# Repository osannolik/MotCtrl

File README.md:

MotCtrl
=========================== 

A small inverter for brushless motors. 

## Hardware

* Microcontroller STM32F446, ARM Cortex-M4, 180 MHz, FPU
* Power MOSFETs 60 V, 300 A, 1.1 mOhm FDBL0110N60
* High- and low-side gate drivers LM5101A
* Inline phase current sensing using INA240 amplifiers
* Hall-sensor inputs
* Standard servo (PPM/PWM) input
* Motor and board temp sensor (NTC)
* Expansion header for UART/ADC/DAC/SPI/I2C/CAN
* PCB size 45x77 mm

# License
GNU GPLv3 (both hardware and experimental software)

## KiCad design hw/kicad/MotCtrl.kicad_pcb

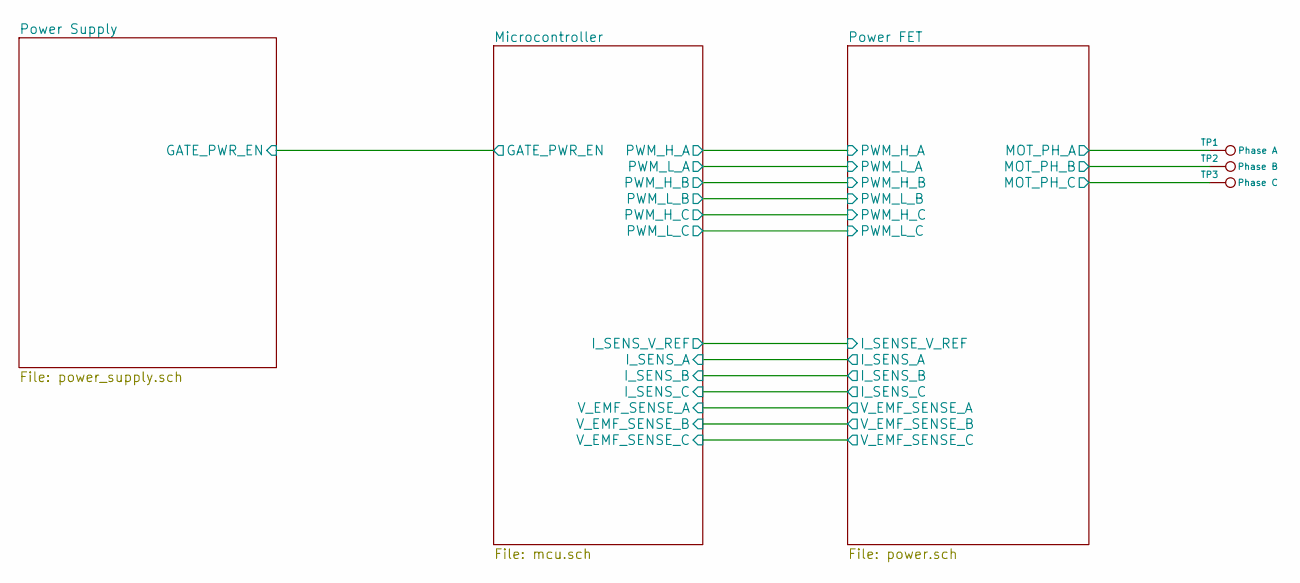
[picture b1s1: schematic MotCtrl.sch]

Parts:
TP1: Phase A; SolderWirePad_single_SMD_5x10mm
TP2: Phase B; SolderWirePad_single_SMD_5x10mm
TP3: Phase C; SolderWirePad_single_SMD_5x10mm

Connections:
/Power FET/MOT_PH_A: TP1.1; also elsewhere on the board
/Power FET/MOT_PH_B: TP2.1; also elsewhere on the board
/Power FET/MOT_PH_C: TP3.1; also elsewhere on the board

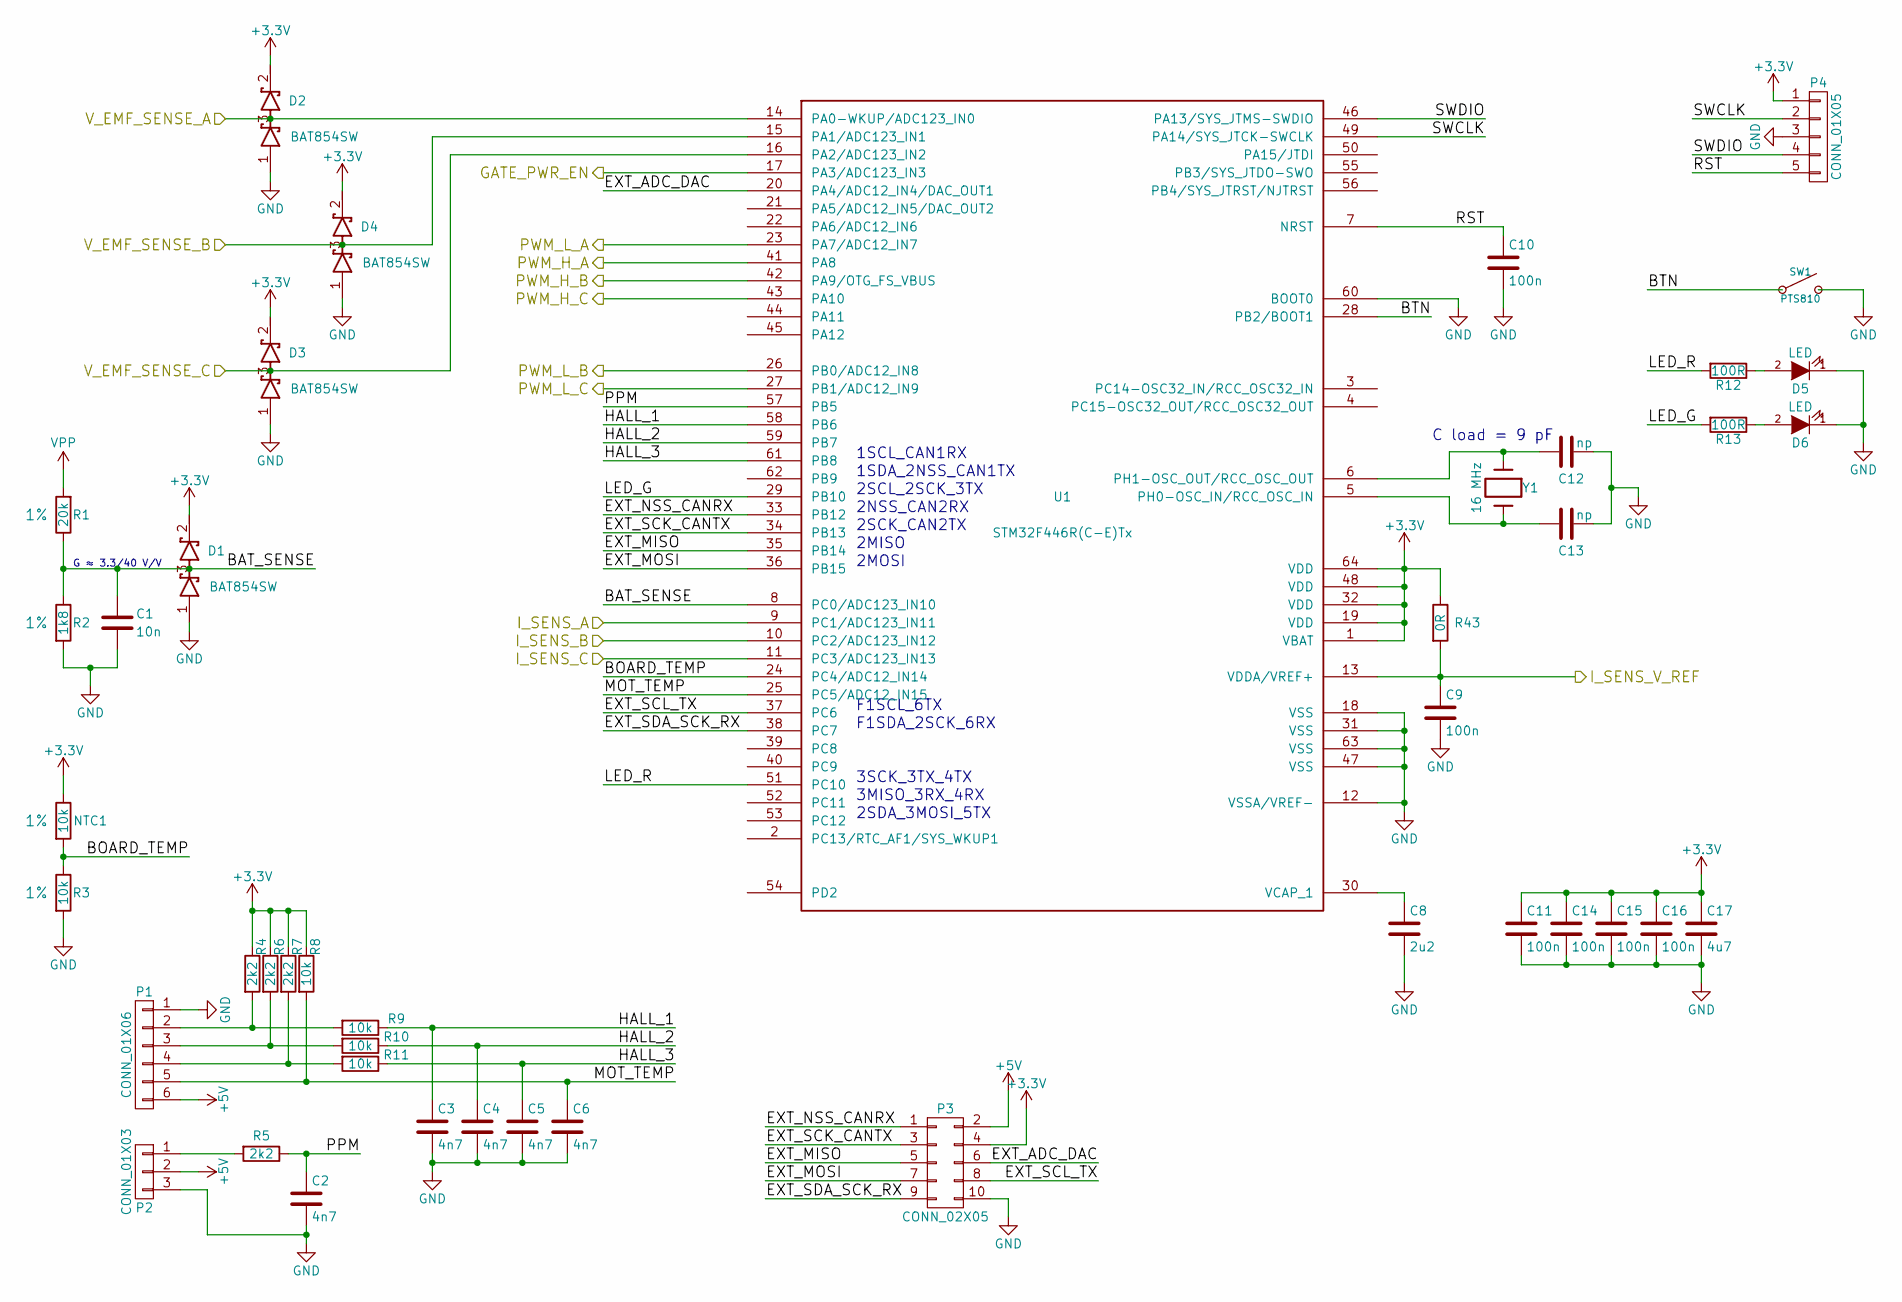
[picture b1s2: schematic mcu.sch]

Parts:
C1: 10n; C_0402
C2, C3, C4, C5, C6: 4n7; C_0402
C8: 2u2; C_0402
C9, C10, C11, C14, C15, C16: 100n; C_0402
C12, C13: np; C_0402
C17: 4u7; C_0603
D1, D2, D3, D4: BAT854SW; SOT-323
D5, D6: LED; LED_0603
NTC1: 10k; R_0603; Tolerance 1%
P1: CONN_01X06; JST_ZH_B6B-ZR
P2: CONN_01X03; Pin_Header_Straight_1x03
P3: CONN_02X05; Pin_Header_Straight_2x05
P4: CONN_01X05; Pin_Header_Straight_1x05
R1: 20k; R_0402; Tolerance 1%
R2: 1k8; R_0402; Tolerance 1%
R3: 10k; R_0402; Tolerance 1%
R4, R5, R6, R7: 2k2; R_0402
R8, R9, R10, R11: 10k; R_0402
R12, R13: 100R; R_0402
R43: 0R; R_0402
SW1: PTS810
U1: STM32F446R(C-E)Tx; LQFP-64_10x10mm_Pitch0.5mm
Y1: 16 MHz; crystal_FA238-TSX3225

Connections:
+3V3: C11.1, C14.1, C15.1, C16.1, C17.1, D1.2 (K), D2.2 (K), D3.2 (K), D4.2 (K), NTC1.1, P3.4, P4.1, R4.1, R6.1, R7.1, R8.1, R43.1, U1.1 (VBAT), U1.19 (VDD), U1.32 (VDD), U1.48 (VDD), U1.64 (VDD); also elsewhere on the board
+5V: P1.6, P2.2, P3.2; also elsewhere on the board
/Microcontroller/BAT_SENSE: C1.1, D1.3 (common), R1.1, R2.1, U1.8 (PC0/ADC123_IN10); also elsewhere on the board
/Microcontroller/BOARD_TEMP: NTC1.2, R3.1, U1.24 (PC4/ADC12_IN14)
/Microcontroller/BTN: SW1.1, SW1.2, U1.28 (PB2/BOOT1)
/Microcontroller/EXT_ADC_DAC: P3.6, U1.20 (PA4/ADC12_IN4/DAC_OUT1)
/Microcontroller/EXT_MISO: P3.5, U1.35 (PB14)
/Microcontroller/EXT_MOSI: P3.7, U1.36 (PB15)
/Microcontroller/EXT_NSS_CANRX: P3.1, U1.33 (PB12)
/Microcontroller/EXT_SCK_CANTX: P3.3, U1.34 (PB13)
/Microcontroller/EXT_SCL_TX: P3.8, U1.37 (PC6)
/Microcontroller/EXT_SDA_SCK_RX: P3.9, U1.38 (PC7)
/Microcontroller/GATE_PWR_EN: U1.17 (PA3/ADC123_IN3); also elsewhere on the board
/Microcontroller/HALL_1: C3.1, R9.1, U1.58 (PB6)
/Microcontroller/HALL_2: C4.1, R10.1, U1.59 (PB7)
/Microcontroller/HALL_3: C5.1, R11.1, U1.61 (PB8)
/Microcontroller/I_SENS_A: U1.9 (PC1/ADC123_IN11); also elsewhere on the board
/Microcontroller/I_SENS_B: U1.10 (PC2/ADC123_IN12); also elsewhere on the board
/Microcontroller/I_SENS_C: U1.11 (PC3/ADC123_IN13); also elsewhere on the board
/Microcontroller/LED_G: R13.2, U1.29 (PB10)
/Microcontroller/LED_R: R12.2, U1.51 (PC10)
/Microcontroller/MOT_TEMP: C6.1, P1.5, R8.2, U1.25 (PC5/ADC12_IN15)
/Microcontroller/PPM: C2.1, R5.1, U1.57 (PB5)
/Microcontroller/PWM_H_A: U1.41 (PA8); also elsewhere on the board
/Microcontroller/PWM_H_B: U1.42 (PA9/OTG_FS_VBUS); also elsewhere on the board
/Microcontroller/PWM_H_C: U1.43 (PA10); also elsewhere on the board
/Microcontroller/PWM_L_A: U1.23 (PA7/ADC12_IN7); also elsewhere on the board
/Microcontroller/PWM_L_B: U1.26 (PB0/ADC12_IN8); also elsewhere on the board
/Microcontroller/PWM_L_C: U1.27 (PB1/ADC12_IN9); also elsewhere on the board
/Microcontroller/RST: C10.1, P4.5, U1.7 (NRST)
/Microcontroller/SWCLK: P4.2, U1.49 (PA14/SYS_JTCK-SWCLK)
/Microcontroller/SWDIO: P4.4, U1.46 (PA13/SYS_JTMS-SWDIO)
/Microcontroller/V_EMF_SENSE_A: D2.3 (common), U1.14 (PA0-WKUP/ADC123_IN0); also elsewhere on the board
/Microcontroller/V_EMF_SENSE_B: D4.3 (common), U1.15 (PA1/ADC123_IN1); also elsewhere on the board
/Microcontroller/V_EMF_SENSE_C: D3.3 (common), U1.16 (PA2/ADC123_IN2); also elsewhere on the board
/Power FET/I_SENSE_V_REF: C9.1, R43.2, U1.13 (VDDA/VREF+); also elsewhere on the board
GND: C1.2, C2.2, C3.2, C4.2, C5.2, C6.2, C8.2, C9.2, C10.2, C11.2, C12.1, C13.1, C14.2, C15.2, C16.2, C17.2, D1.1 (A), D2.1 (A), D3.1 (A), D4.1 (A), D5.1 (K), D6.1 (K), P1.1, P2.3, P3.10, P4.3, R2.2, R3.2, SW1.3, SW1.4, U1.12 (VSSA/VREF-), U1.18 (VSS), U1.31 (VSS), U1.47 (VSS), U1.60 (BOOT0), U1.63 (VSS); also elsewhere on the board
unnamed: C8.1, U1.30 (VCAP_1)
unnamed: C12.2, U1.6 (PH1-OSC_OUT/RCC_OSC_OUT), Y1.1
unnamed: C13.2, U1.5 (PH0-OSC_IN/RCC_OSC_IN), Y1.2
unnamed: D5.2 (A), R12.1
unnamed: D6.2 (A), R13.1
unnamed: P1.2, R4.2, R9.2
unnamed: P1.3, R6.2, R10.2
unnamed: P1.4, R7.2, R11.2
unnamed: P2.1, R5.2
VPP: R1.2; also elsewhere on the board

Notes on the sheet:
C load = 9 pF
G ≈ 3.3/40 V/V
1SCL_CAN1RX
1SDA_2NSS_CAN1TX
2SCL_2SCK_3TX
2NSS_CAN2RX
2SCK_CAN2TX
2MISO
2MOSI
F1SCL_6TX
F1SDA_2SCK_6RX
3SCK_3TX_4TX
3MISO_3RX_4RX
2SDA_3MOSI_5TX

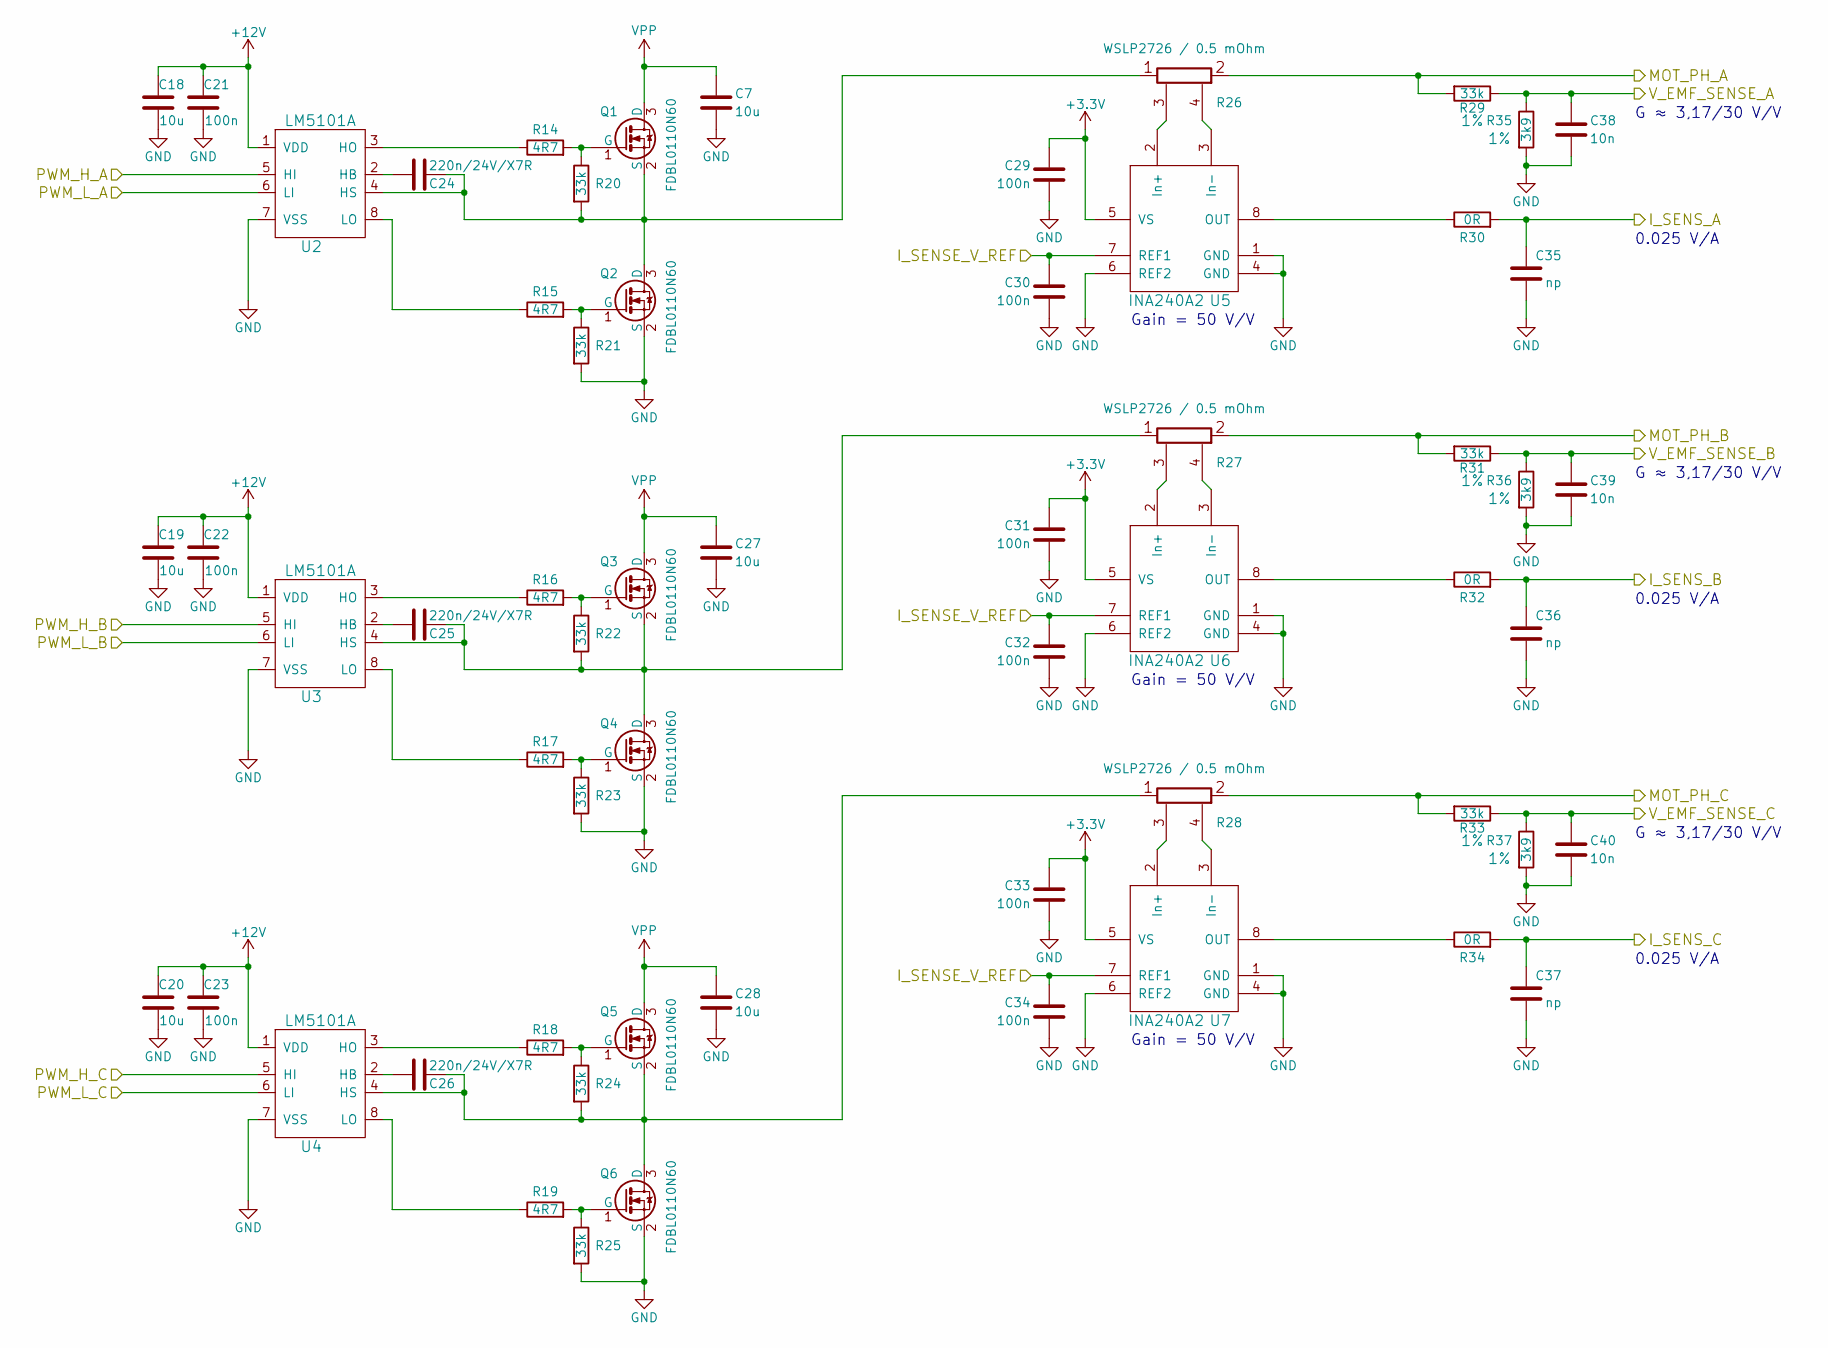
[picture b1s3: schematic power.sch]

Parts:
C7, C27, C28: 10u; C_1210
C18, C19, C20: 10u; C_0805
C21, C22, C23, C29, C30, C31, C32, C33, C34: 100n; C_0402
C24, C25, C26: 220n/24V/X7R; C_0603
C35, C36, C37: np; C_0402
C38, C39, C40: 10n; C_0402
Q1, Q2, Q3, Q4, Q5, Q6: FDBL0110N60; MO-299A
R14, R15, R16, R17, R18, R19: 4R7; R_0402
R20, R21, R22, R23, R24, R25: 33k; R_0402
R26, R27, R28: WSLP2726 / 0.5 mOhm; WSLP2726
R29, R31, R33: 33k; R_0402; Tolerance 1%
R30, R32, R34: 0R; R_0402
R35, R36, R37: 3k9; R_0402; Tolerance 1%
U2, U3, U4: LM5101A; WSON-8
U5, U6, U7: INA240A2; TSSOP-8_4.4x3mm_Pitch0.65mm

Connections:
+3V3: C29.2, C31.2, C33.2, U5.5 (VS), U6.5 (VS), U7.5 (VS); also elsewhere on the board
+12V: C18.2, C19.2, C20.2, C21.2, C22.2, C23.2, U2.1 (VDD), U3.1 (VDD), U4.1 (VDD); also elsewhere on the board
/Microcontroller/I_SENS_A: C35.2, R30.2; also elsewhere on the board
/Microcontroller/I_SENS_B: C36.2, R32.2; also elsewhere on the board
/Microcontroller/I_SENS_C: C37.2, R34.2; also elsewhere on the board
/Microcontroller/PWM_H_A: U2.5 (HI); also elsewhere on the board
/Microcontroller/PWM_H_B: U3.5 (HI); also elsewhere on the board
/Microcontroller/PWM_H_C: U4.5 (HI); also elsewhere on the board
/Microcontroller/PWM_L_A: U2.6 (LI); also elsewhere on the board
/Microcontroller/PWM_L_B: U3.6 (LI); also elsewhere on the board
/Microcontroller/PWM_L_C: U4.6 (LI); also elsewhere on the board
/Microcontroller/V_EMF_SENSE_A: C38.1, R29.1, R35.1; also elsewhere on the board
/Microcontroller/V_EMF_SENSE_B: C39.1, R31.1, R36.1; also elsewhere on the board
/Microcontroller/V_EMF_SENSE_C: C40.1, R33.1, R37.1; also elsewhere on the board
/Power FET/I_SENSE_V_REF: C30.2, C32.2, C34.2, U5.7 (REF1), U6.7 (REF1), U7.7 (REF1); also elsewhere on the board
/Power FET/MOT_PH_A: R26.2, R29.2; also elsewhere on the board
/Power FET/MOT_PH_B: R27.2, R31.2; also elsewhere on the board
/Power FET/MOT_PH_C: R28.2, R33.2; also elsewhere on the board
/Power FET/PH_A: C24.1, Q1.2 (S), Q2.3 (D), R20.2, R26.1, U2.4 (HS)
/Power FET/PH_B: C25.1, Q3.2 (S), Q4.3 (D), R22.2, R27.1, U3.4 (HS)
/Power FET/PH_C: C26.1, Q5.2 (S), Q6.3 (D), R24.2, R28.1, U4.4 (HS)
GND: C7.2, C18.1, C19.1, C20.1, C21.1, C22.1, C23.1, C27.2, C28.2, C29.1, C30.1, C31.1, C32.1, C33.1, C34.1, C35.1, C36.1, C37.1, C38.2, C39.2, C40.2, Q2.2 (S), Q4.2 (S), Q6.2 (S), R21.2, R23.2, R25.2, R35.2, R36.2, R37.2, U2.7 (VSS), U3.7 (VSS), U4.7 (VSS), U5.1 (GND), U5.4 (GND), U5.6 (REF2), U6.1 (GND), U6.4 (GND), U6.6 (REF2), U7.1 (GND), U7.4 (GND), U7.6 (REF2); also elsewhere on the board
unnamed: C24.2, U2.2 (HB)
unnamed: C25.2, U3.2 (HB)
unnamed: C26.2, U4.2 (HB)
unnamed: Q1.1 (G), R14.2, R20.1
unnamed: Q2.1 (G), R15.2, R21.1
unnamed: Q3.1 (G), R16.2, R22.1
unnamed: Q4.1 (G), R17.2, R23.1
unnamed: Q5.1 (G), R18.2, R24.1
unnamed: Q6.1 (G), R19.2, R25.1
unnamed: R14.1, U2.3 (HO)
unnamed: R15.1, U2.8 (LO)
unnamed: R16.1, U3.3 (HO)
unnamed: R17.1, U3.8 (LO)
unnamed: R18.1, U4.3 (HO)
unnamed: R19.1, U4.8 (LO)
unnamed: R26.3, U5.2 (In+)
unnamed: R26.4, U5.3 (In-)
unnamed: R27.3, U6.2 (In+)
unnamed: R27.4, U6.3 (In-)
unnamed: R28.3, U7.2 (In+)
unnamed: R28.4, U7.3 (In-)
unnamed: R30.1, U5.8 (OUT)
unnamed: R32.1, U6.8 (OUT)
unnamed: R34.1, U7.8 (OUT)
VPP: C7.1, C27.1, C28.1, Q1.3 (D), Q3.3 (D), Q5.3 (D); also elsewhere on the board

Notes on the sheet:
Gain = 50 V/V
0.025 V/A
G ≈ 3,17/30 V/V

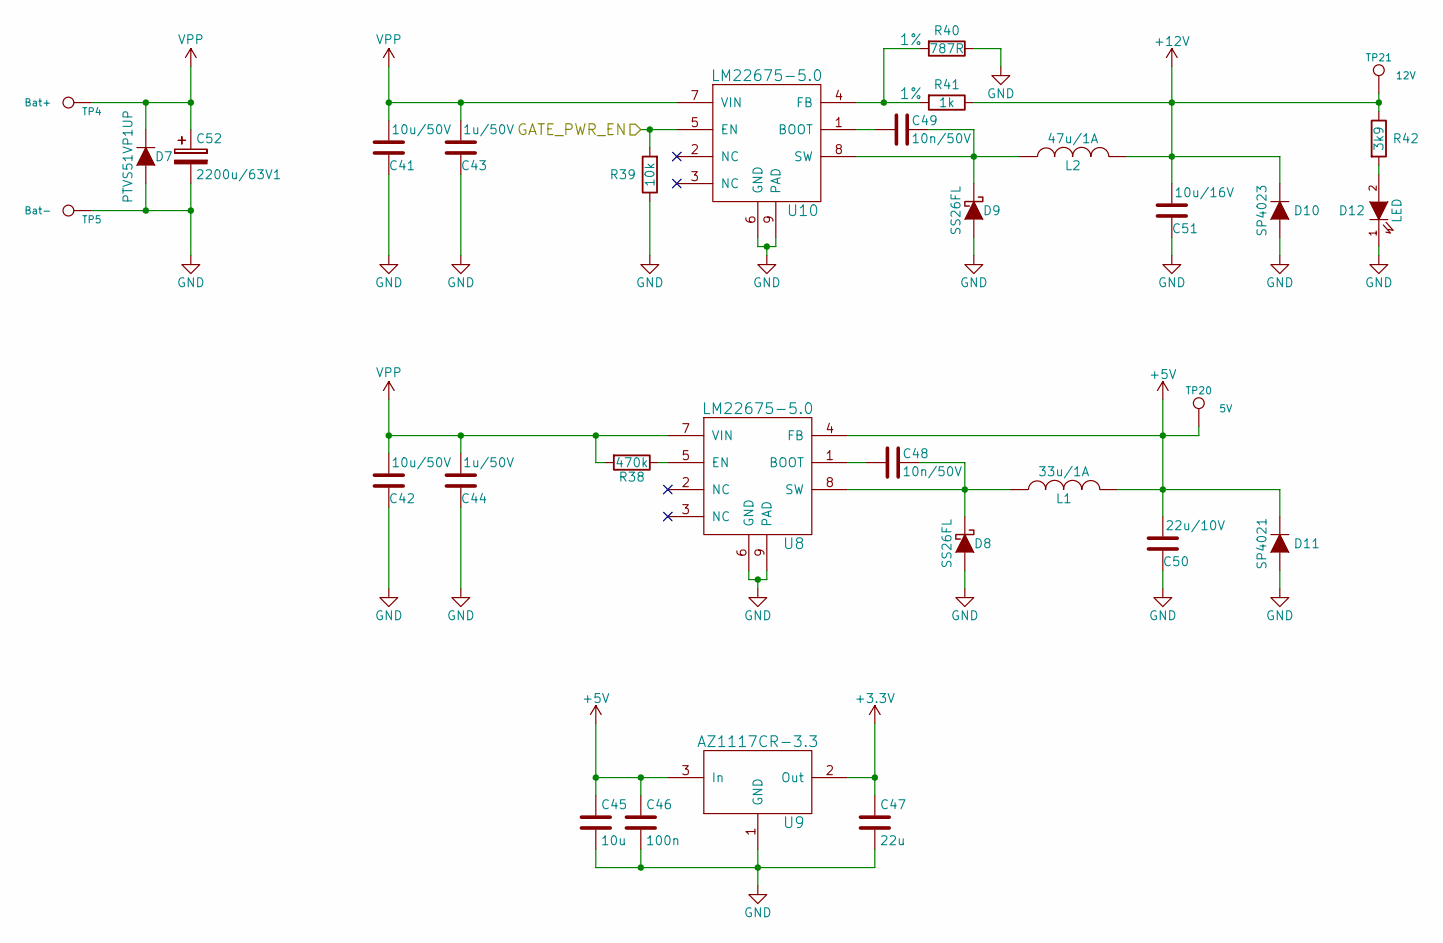
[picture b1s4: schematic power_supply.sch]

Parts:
C41, C42: 10u/50V; C_1210
C43, C44: 1u/50V; C_0805
C45: 10u; C_0805
C46: 100n; C_0402
C47: 22u; C_0805
C48, C49: 10n/50V; C_0402
C50: 22u/10V; C_0805
C51: 10u/16V; C_0805
C52: 2200u/63V1; C_Radial_D18_L37_P7.5_Angled
D7: PTVS51VP1UP; SOD-128
D8, D9: SS26FL; SOD-123
D10: SP4023; SOD-323
D11: SP4021; SOD-323
D12: LED; LED_0603
L1: 33u/1A; SRN8040TA
L2: 47u/1A; SRN8040TA
R38: 470k; R_0402
R39: 10k; R_0402
R40: 787R; R_0402; Tolerance 1%
R41: 1k; R_0402; Tolerance 1%
R42: 3k9; R_0402
TP4: Bat+; SolderWirePad_single_SMD_5x5mm
TP5: Bat-; SolderWirePad_single_SMD_5x5mm
TP20: 5V; Measurement_Point_Round-SMD-Pad_Small
TP21: 12V; Measurement_Point_Round-SMD-Pad_Small
U8, U10: LM22675-5.0; HSOP-8
U9: AZ1117CR-3.3; SOT89-3_Housing

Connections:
+3V3: C47.1, U9.2 (Out); also elsewhere on the board
+5V: C45.1, C46.1, C50.2, D11.1 (K), L1.2, TP20.1, U8.4 (FB), U9.3 (In); also elsewhere on the board
+12V: C51.2, D10.1 (K), L2.2, R41.1, R42.1, TP21.1; also elsewhere on the board
/Microcontroller/GATE_PWR_EN: R39.2, U10.5 (EN); also elsewhere on the board
GND: C41.1, C42.1, C43.1, C44.1, C45.2, C46.2, C47.2, C50.1, C51.1, C52.2, D7.2 (A), D8.2 (A), D9.2 (A), D10.2 (A), D11.2 (A), D12.1 (K), R39.1, R40.1, TP5.1, U8.6 (GND), U8.9 (PAD), U9.1 (GND), U10.6 (GND), U10.9 (PAD); also elsewhere on the board
unnamed: C48.1, D8.1 (K), L1.1, U8.8 (SW)
unnamed: C48.2, U8.1 (BOOT)
unnamed: C49.1, D9.1 (K), L2.1, U10.8 (SW)
unnamed: C49.2, U10.1 (BOOT)
unnamed: D12.2 (A), R42.2
unnamed: R38.1, U8.5 (EN)
unnamed: R40.2, R41.2, U10.4 (FB)
VPP: C41.2, C42.2, C43.2, C44.2, C52.1, D7.1 (K), R38.2, TP4.1, U8.7 (VIN), U10.7 (VIN); also elsewhere on the board

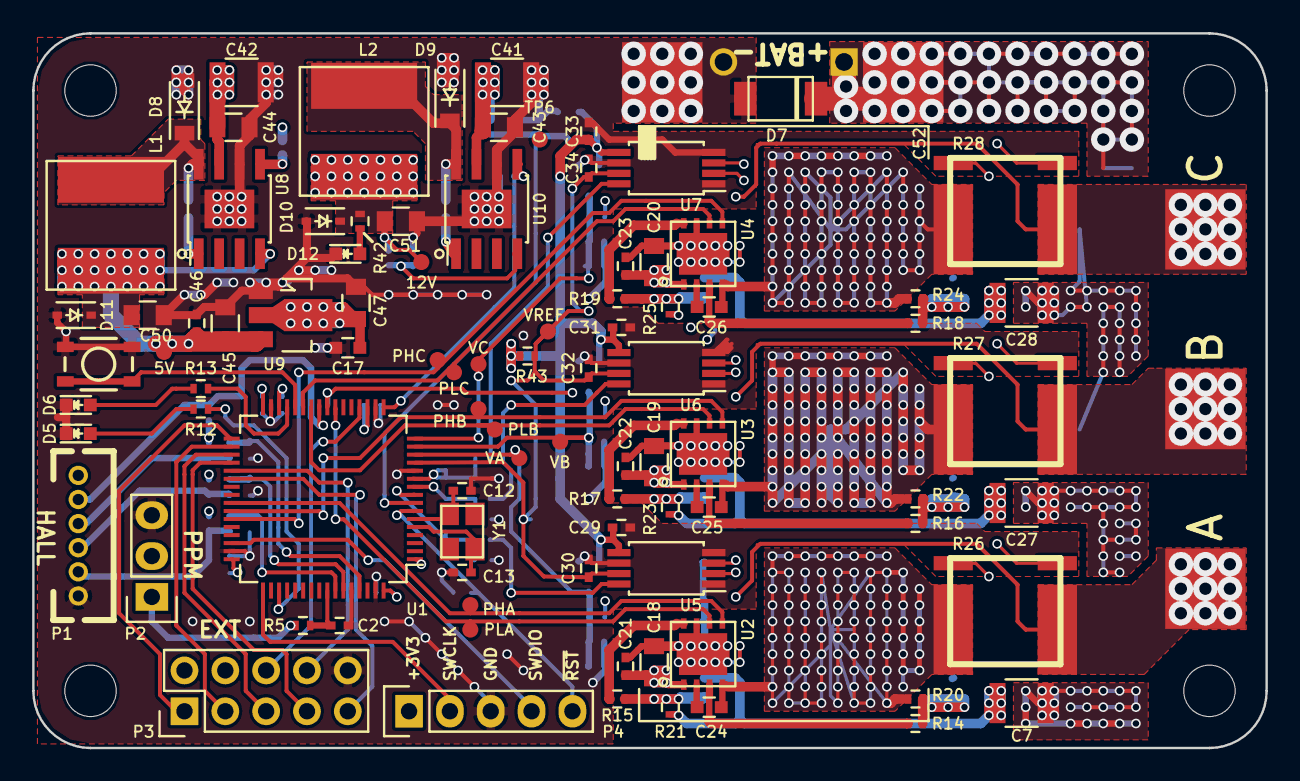
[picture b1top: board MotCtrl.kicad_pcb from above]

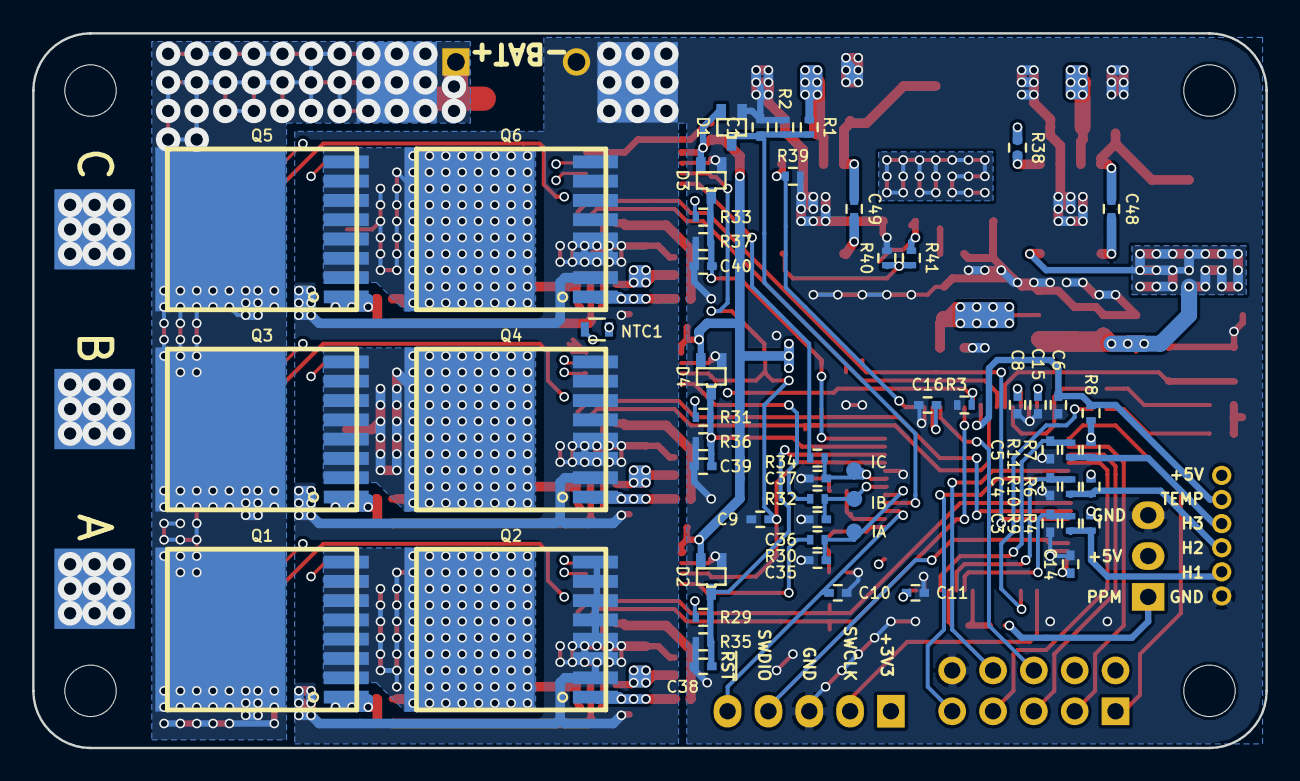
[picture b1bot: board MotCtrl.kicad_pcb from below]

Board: 4 copper layers, 76.7 x 44.5 mm, 158 parts (62 on the bottom side), 85 nets.

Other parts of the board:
TP1#2: Phase A; SolderWirePad_single_SMD_5x5mm
TP2#2: Phase B; SolderWirePad_single_SMD_5x5mm
TP3#2: Phase C; SolderWirePad_single_SMD_5x5mm
TP4#2: Bat+; SolderWirePad_single_SMD_5x5mm
TP5#2: Bat-; SolderWirePad_single_SMD_5x5mm
TP6: BAT_SENSE; Measurement_Point_Round-SMD-Pad_Small
TP7: VA; Measurement_Point_Round-SMD-Pad_Small
TP8: IA; Measurement_Point_Round-SMD-Pad_Small
TP9: VB; Measurement_Point_Round-SMD-Pad_Small
TP10: IB; Measurement_Point_Round-SMD-Pad_Small
TP11: VC; Measurement_Point_Round-SMD-Pad_Small
TP12: IC; Measurement_Point_Round-SMD-Pad_Small
TP13: VREF; Measurement_Point_Round-SMD-Pad_Small
TP14: PHA; Measurement_Point_Round-SMD-Pad_Small
TP15: PHB; Measurement_Point_Round-SMD-Pad_Small
TP16: PHC; Measurement_Point_Round-SMD-Pad_Small
TP17: PLA; Measurement_Point_Round-SMD-Pad_Small
TP18: PLB; Measurement_Point_Round-SMD-Pad_Small
TP19: PLC; Measurement_Point_Round-SMD-Pad_Small

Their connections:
/Microcontroller/BAT_SENSE: TP6.1; also elsewhere on the board
/Microcontroller/I_SENS_A: TP8.1; also elsewhere on the board
/Microcontroller/I_SENS_B: TP10.1; also elsewhere on the board
/Microcontroller/I_SENS_C: TP12.1; also elsewhere on the board
/Microcontroller/PWM_H_A: TP14.1; also elsewhere on the board
/Microcontroller/PWM_H_B: TP15.1; also elsewhere on the board
/Microcontroller/PWM_H_C: TP16.1; also elsewhere on the board
/Microcontroller/PWM_L_A: TP17.1; also elsewhere on the board
/Microcontroller/PWM_L_B: TP18.1; also elsewhere on the board
/Microcontroller/PWM_L_C: TP19.1; also elsewhere on the board
/Microcontroller/V_EMF_SENSE_A: TP7.1; also elsewhere on the board
/Microcontroller/V_EMF_SENSE_B: TP9.1; also elsewhere on the board
/Microcontroller/V_EMF_SENSE_C: TP11.1; also elsewhere on the board
/Power FET/I_SENSE_V_REF: TP13.1; also elsewhere on the board
/Power FET/MOT_PH_A: TP1#2.1; also elsewhere on the board
/Power FET/MOT_PH_B: TP2#2.1; also elsewhere on the board
/Power FET/MOT_PH_C: TP3#2.1; also elsewhere on the board
GND: TP5#2.1; also elsewhere on the board
VPP: TP4#2.1; also elsewhere on the board

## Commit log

2016-10-29 Initiating repo
2016-10-29 Started kicad project
2016-10-30 First steps on gate driver circuit
2016-11-04 Added power mosfet footprint
2016-11-04 Some more work on the FET-stage
2016-11-05 More power work
2016-11-05 Add missing files
2016-11-06 Connect mcu to drv8301
2016-11-09 Added LDO for mcu
2016-11-11 work
2016-11-12 Big changes in power: new mosfets, drivers and current sensing
2016-11-20 Started working on power supplies
2016-11-20 Map INA240 to footprint
2016-11-21 Gate power supply enabling and board temp sensor
2016-11-22 cleaned out unused footprints
2016-11-22 TVS across bat connection
2016-11-23 Bat pads and leds
2016-11-25 Connected and shuffled around mcu pins
2016-11-26 TVS on 5V and 3.3V rails
2016-11-26 Annotation
2016-11-26 Map footprints to components and add BOM
2016-11-27 Started playing around with layout
2016-11-29 More layout tryouts
2016-11-30 Aligned first power draft
2016-11-30 Alternative layout with smaller total vertical footprint
2016-12-01 Yet another alternative
2016-12-03 Go ahead with lower layout
2016-12-03 Som smaller fixes to lower layout
2016-12-03 Started duplicating and aligning power stages
2016-12-07 Aligned, started rework current shunt layout and copper pour
2016-12-10 First draft of power stage placed and routed
2016-12-10 Changed footprint of and placed bulk cap
2016-12-11 Placing power supply components
2016-12-11 Changed footprint of hall sensor contact and placed more components
2016-12-12 Routed power supply
2016-12-13 Routed EMF and I sense to mcu
2016-12-13 First draft of completely routed board
2016-12-15 Forgot some traces...
2016-12-17 Rounded corners
2016-12-18 Added current sense voltage reference as reparate net again
2016-12-18 Silkscreen placed correctly
2016-12-18 Add test pads
2016-12-19 Revision A sent to fab
2017-02-10 First version of an elementary BLDC controller
2017-02-18 Change to center-aligned PWM
2017-02-19 Edge aligned PWM. Started to experiment with current and BEMF measurements.
2017-02-26 Changed PWM freq to 20k. Added ability to output sampled values to DAC.
2017-02-26 HW: Changed rc-filter capacitor to increase BEMF-sense bandwidth.
2017-03-13 0 deg hall offset motor support ONLY
2017-03-18 Work, hall sensor speed measurement
2017-03-18 Reconfigured timer for speed estimation and commutation
2017-03-19 Arbitrary hall sensor offset (0-30 deg) supported
2017-03-20 Determine direction based on current and previous hall state
2017-03-21 Experimenting with angle estimation inbetween hall state changes
2017-03-22 Handle speed timer overflow
2017-04-07 Improved robustness and overhead in com
2017-04-08 Removed hardcoded DMA instance, partially...
2017-04-08 CRC on tx frames is now possible
2017-04-08 Oops, conditional include incorrect.
2017-04-15 Added measurement of board temp and bat voltage
2017-04-18 Temp measurement sample rate and adc sampling time
2017-04-20 Restructured in order to minimize module dependencies
2017-04-23 Total current test
2017-04-27 Small restructure of duty flow. Better handling of sample triggering.
2017-04-29 Separated 6-step related stuff from general inverter system
2017-04-29 Rename bldc file and functions
2017-04-30 Add simple speed control
2017-05-13 Experimenting with bipolar pwm
2017-06-03 Position refactoring work. Add Encoder as another sensor. Untested.
2017-06-05 Position is electrical angle
2017-06-06 Hall-mode tested after position refactoring
2017-06-24 Testing code analysis tool...
2017-06-24 Prepare for foc
2017-07-12 foc kind of works... cleanup needed!
